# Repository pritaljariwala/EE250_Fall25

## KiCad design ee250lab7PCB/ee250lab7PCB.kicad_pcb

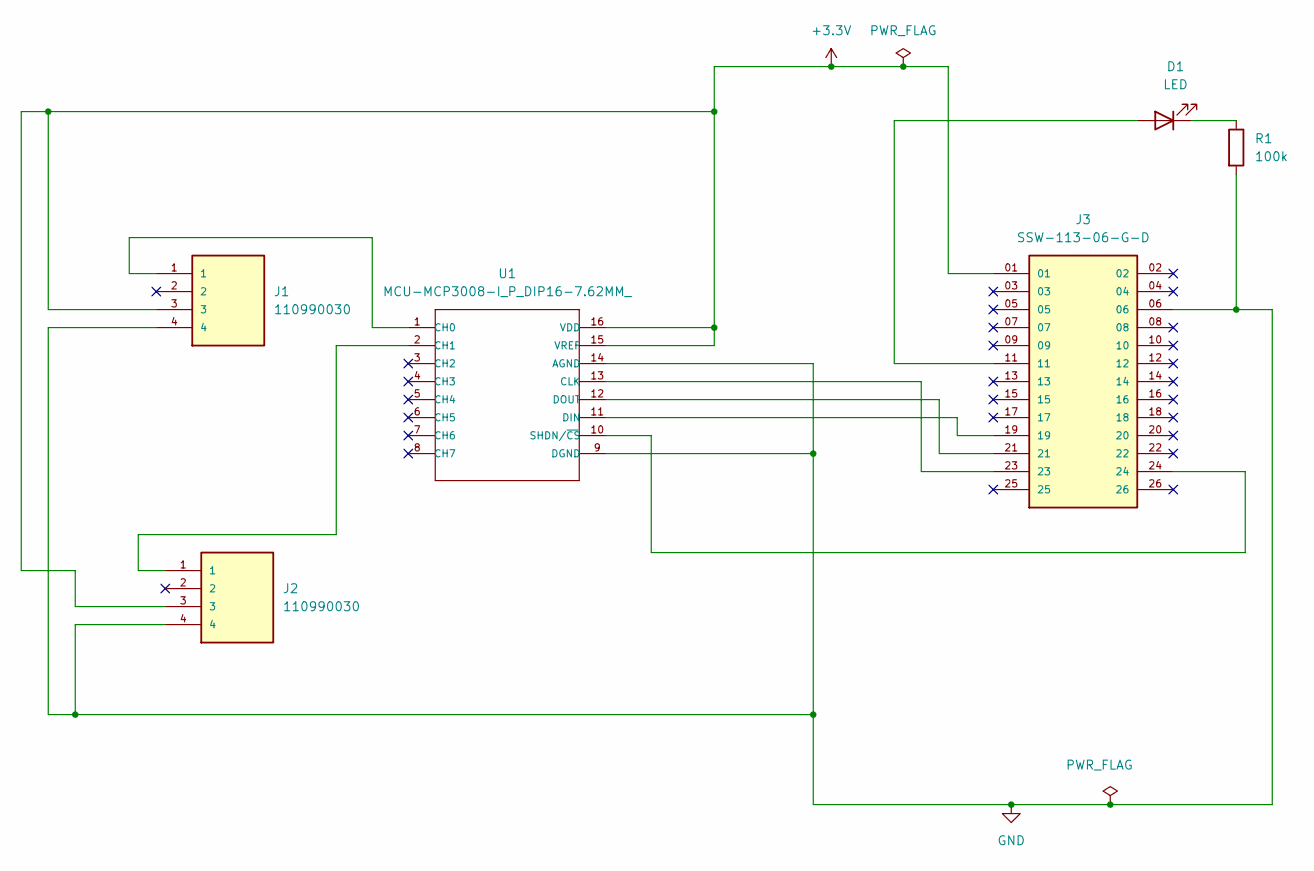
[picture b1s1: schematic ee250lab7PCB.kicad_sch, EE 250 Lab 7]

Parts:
D1: LED; LED_D5.0mm
J1, J2: 110990030; SEEED_110990030; PARTREV A
J3: SSW-113-06-G-D; SAMTEC_SSW-113-06-G-D; PARTREV R
R1: 100k; R_Axial_DIN0204_L3.6mm_D1.6mm_P7.62mm_Horizontal
U1: MCU-MCP3008-I_P_DIP16-7.62MM_; DIP16-2.54-19.2X7.62MM; MPN MCP3008-I/P

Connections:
+3.3V: J1.3, J2.3, J3.01, U1.15 (VREF), U1.16 (VDD)
GND: J1.4, J2.4, J3.06, R1.2, U1.9 (DGND), U1.14 (AGND)
unnamed: D1.2 (A), J3.11
unnamed: D1.1 (K), R1.1
unnamed: J1.1, U1.1 (CH0)
unnamed: J2.1, U1.2 (CH1)
unnamed: J3.23, U1.13 (CLK)
unnamed: J3.19, U1.11 (DIN)
unnamed: J3.21, U1.12 (DOUT)
unnamed: J3.24, U1.10 (SHDN/~CS)

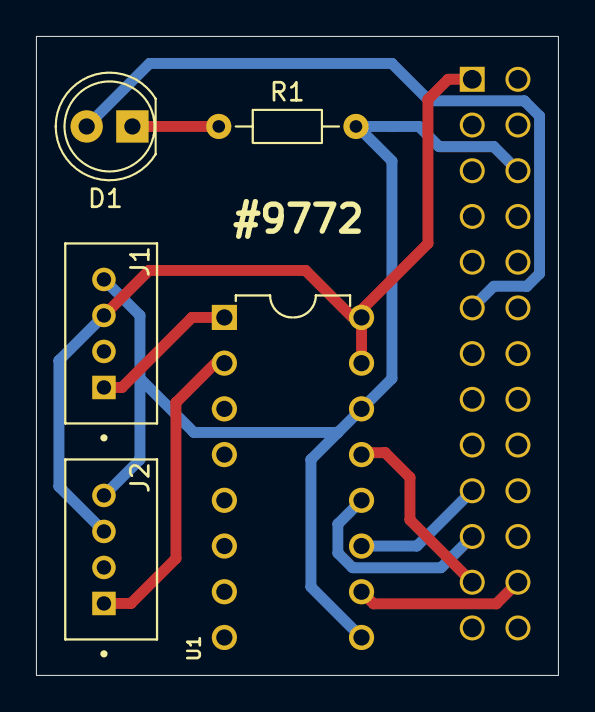
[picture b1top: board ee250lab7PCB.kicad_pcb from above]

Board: 2 copper layers, 29.0 x 35.5 mm, 6 parts (1 on the bottom side), 10 nets.

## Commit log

2025-09-24 lab3 initial commit
2025-09-30 Lab 4
2025-09-30 Lab 4 update
2025-09-30 names added
2025-10-14 ee250 lab 5 initial commit
2025-10-14 10/14 5 pm
2025-10-15 9:40 pm
2025-10-20 initial commit lab6
2025-10-20 edited
2025-10-20 works but the screen blinks
2025-10-21 lab 7 initial commit
2025-10-22 sound sensor stuff (not fully done)
2025-10-22 Created lab6writeup.md with lab details
2025-10-28 please work
2025-10-28 +add to folder
2025-10-29 test
2025-11-04 lab8
2025-11-04 finished lab 8 subpart
2025-11-05 readme for lab 8
